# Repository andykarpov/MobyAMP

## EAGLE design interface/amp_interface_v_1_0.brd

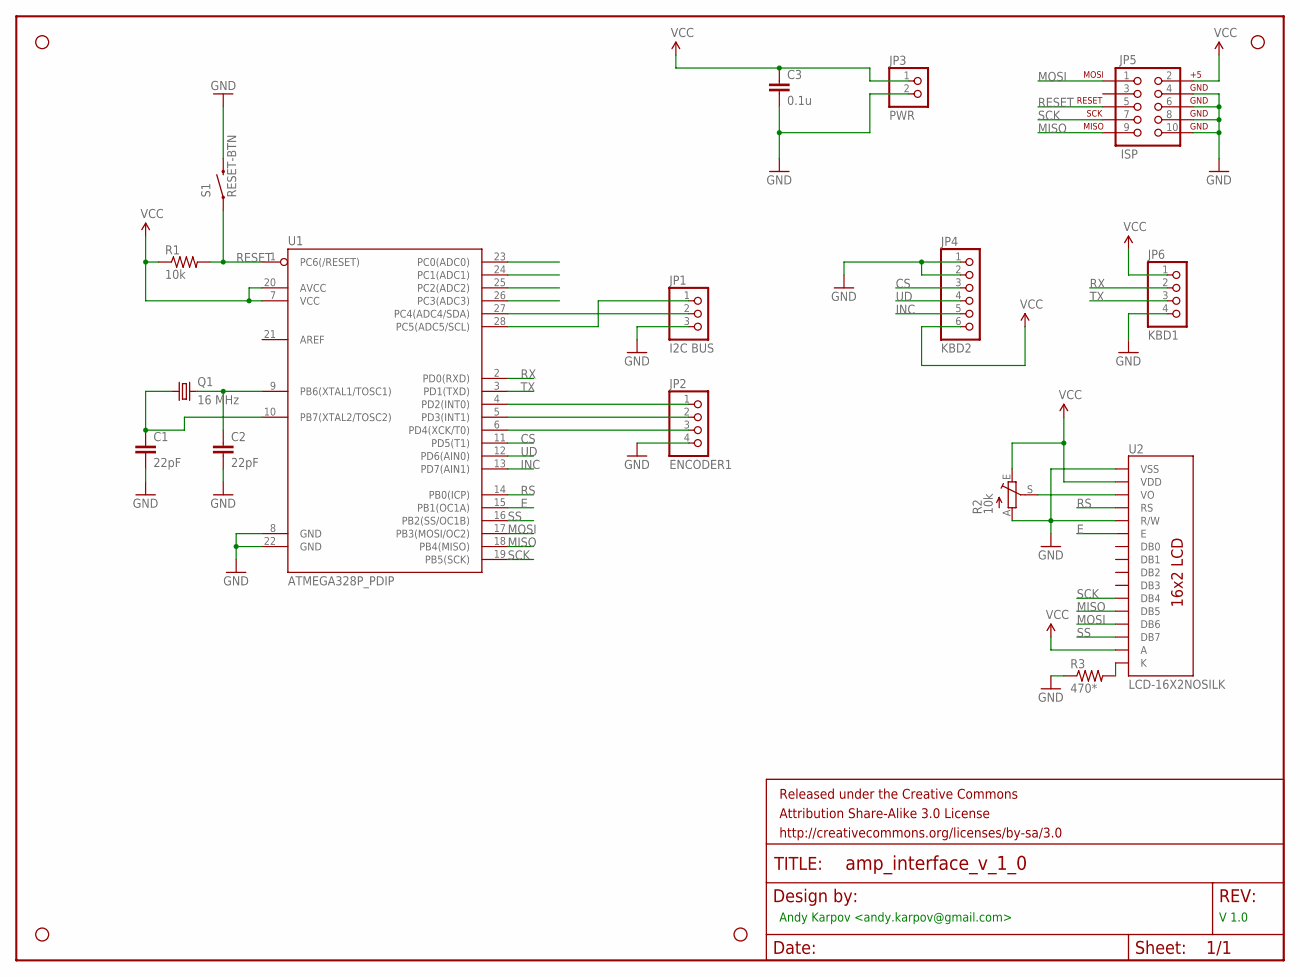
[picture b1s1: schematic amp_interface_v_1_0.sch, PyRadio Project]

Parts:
C1, C2: 22pF; CAP-PTH-SMALL2
C3: 0.1u; CAP-PTH-SMALL2
FRAME1: FRAME-LETTER; CREATIVE_COMMONS
JP1: I2C BUS; 1X03
JP2: ENCODER1; 1X04
JP3: PWR; 1X02
JP4: KBD2; 1X06
JP5: ISP; 2X5-SHROUDED
JP6: KBD1; 1X04
Q1: 16 MHz; HC49/S
R1: 10k; AXIAL-0.4
R2: 10k; B64Y
R3: 470*; AXIAL-0.4
S1: RESET-BTN; TACTILE-PTH
STANDOFF1, STANDOFF2, STANDOFF3, STANDOFF4: STAND-OFF
U1: ATMEGA328P_PDIP; DIL28-3
U2: LCD-16X2NOSILK; LCD-16X2_NOSILK

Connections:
CS: JP4.3, U1.11 (PD5(T1))
E: U1.15 (PB1(OC1A)), U2.6 (E)
GND: C1.2, C2.2, C3.2, JP1.3, JP2.4, JP3.2, JP4.1, JP4.2, JP5.4, JP5.6, JP5.8, JP5.10, JP6.4, R2.A, R3.P$1 (1), S1.3 (2), U1.8 (GND), U1.22 (GND), U2.1 (VSS), U2.5 (R/W)
INC: JP4.5, U1.13 (PD7(AIN1))
MISO: JP5.9, U1.18 (PB4(MISO)), U2.12 (DB5)
MOSI: JP5.1, U1.17 (PB3(MOSI/OC2)), U2.13 (DB6)
unnamed: C2.1, Q1.2, U1.9 (PB6(XTAL1/TOSC1))
unnamed: C1.1, Q1.1, U1.10 (PB7(XTAL2/TOSC2))
unnamed: R2.S, U2.3 (VO)
unnamed: R3.P$2 (2), U2.16 (K)
unnamed: JP1.2, U1.27 (PC4(ADC4/SDA))
unnamed: JP1.1, U1.28 (PC5(ADC5/SCL))
unnamed: JP2.3, U1.6 (PD4(XCK/T0))
unnamed: JP2.1, U1.4 (PD2(INT0))
unnamed: JP2.2, U1.5 (PD3(INT1))
PC0: U1.23 (PC0(ADC0))
PC1: U1.24 (PC1(ADC1))
PC2: U1.25 (PC2(ADC2))
PC3: U1.26 (PC3(ADC3))
RESET: JP5.5, R1.P$2 (2), S1.1, U1.1 (PC6(/RESET))
RS: U1.14 (PB0(ICP)), U2.4 (RS)
RX: JP6.2, U1.2 (PD0(RXD))
SCK: JP5.7, U1.19 (PB5(SCK)), U2.11 (DB4)
SS: U1.16 (PB2(SS/OC1B)), U2.14 (DB7)
TX: JP6.3, U1.3 (PD1(TXD))
UD: JP4.4, U1.12 (PD6(AIN0))
VCC: C3.1, JP3.1, JP4.6, JP5.2, JP6.1, R1.P$1 (1), R2.E, U1.7 (VCC), U1.20 (AVCC), U2.2 (VDD), U2.15 (A)

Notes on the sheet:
Andy Karpov <andy.karpov@gmail.com>
V 1.0

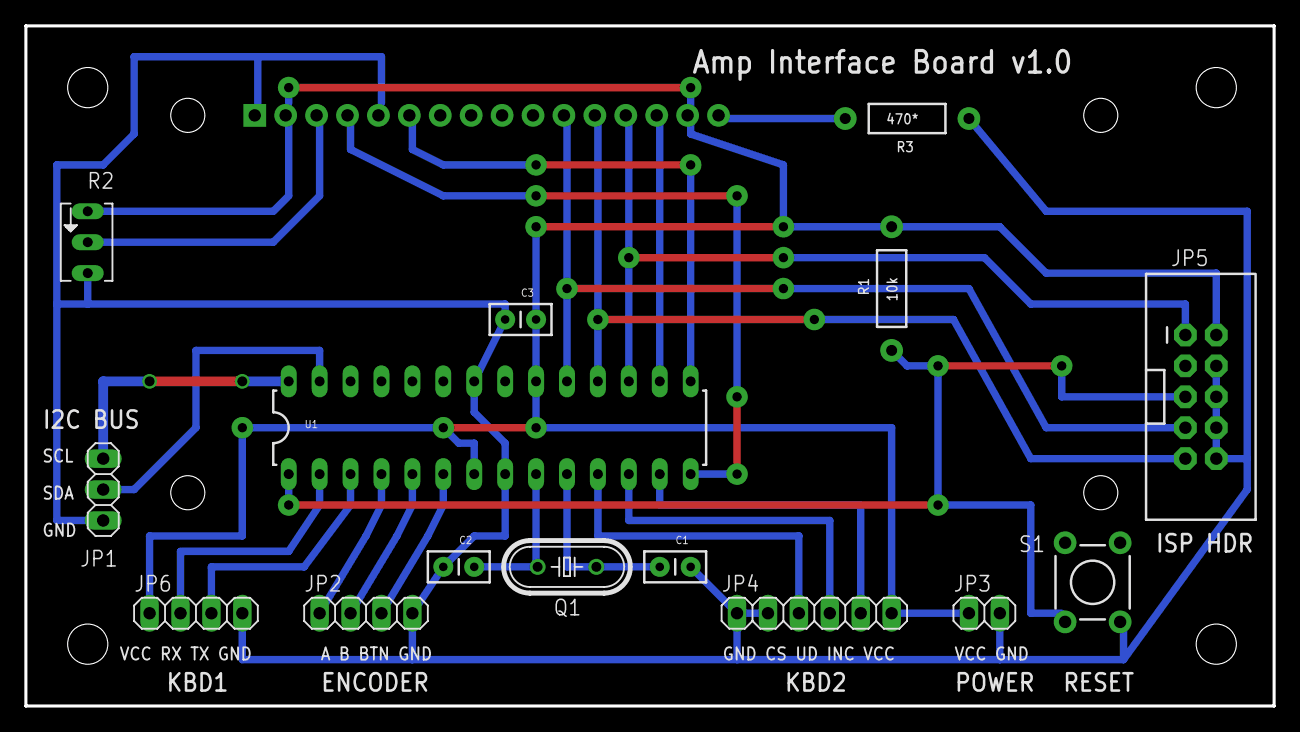
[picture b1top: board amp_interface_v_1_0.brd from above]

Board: 2 copper layers, 102.5 x 55.9 mm, 21 parts (0 on the bottom side), 23 nets.

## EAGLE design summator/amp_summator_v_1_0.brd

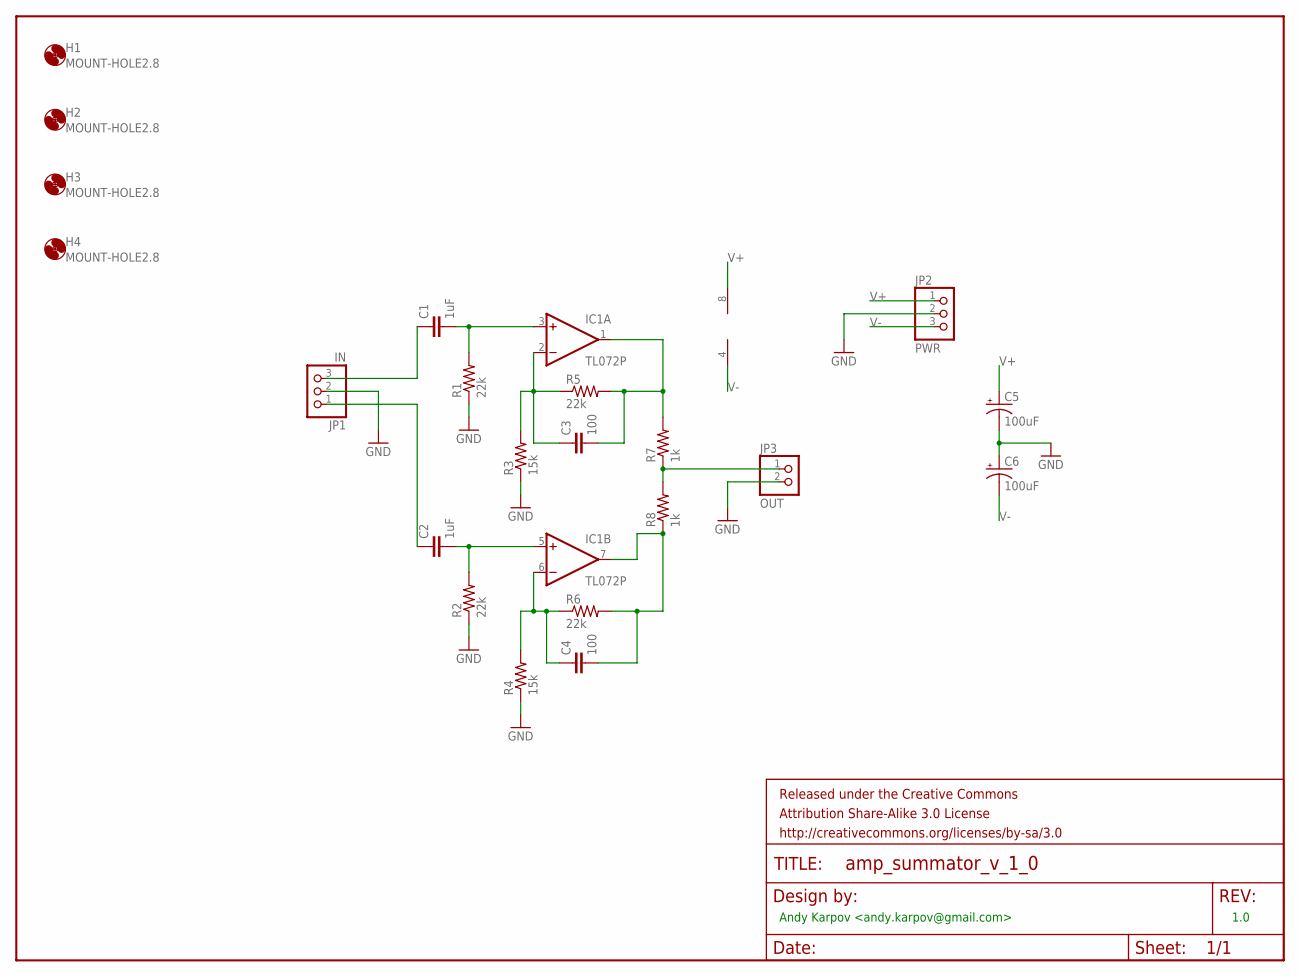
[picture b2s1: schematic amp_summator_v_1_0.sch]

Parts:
C1, C2: 1uF; CAP-PTH-5MM
C3, C4: 100; CAP-PTH-5MM
C5, C6: 100uF; CPOL-RADIAL-100UF-25V
FRAME1: FRAME-LETTER; CREATIVE_COMMONS
H1, H2, H3, H4: MOUNT-HOLE2.8; 2,8
IC1: TL072P; DIL08
JP1: IN; 1X03
JP2: PWR; 1X03
JP3: OUT; 1X02
R1, R2, R5, R6: 22k; AXIAL-0.4
R3, R4: 15k; AXIAL-0.4
R7, R8: 1k; AXIAL-0.4

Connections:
GND: C5.2 (-), C6.1 (+), JP1.2, JP2.2, JP3.2, R1.P$1 (1), R2.P$1 (1), R3.P$1 (1), R4.P$1 (1)
unnamed: C1.1, JP1.3
unnamed: JP3.1, R7.P$1 (1), R8.P$2 (2)
unnamed: C3.2, IC1.1 (OUT), R5.P$2 (2), R7.P$2 (2)
unnamed: C4.2, IC1.7 (OUT), R6.P$2 (2), R8.P$1 (1)
unnamed: C3.1, IC1.2 (-IN), R3.P$2 (2), R5.P$1 (1)
unnamed: C1.2, IC1.3 (+IN), R1.P$2 (2)
unnamed: C2.1, JP1.1
unnamed: C2.2, IC1.5 (+IN), R2.P$2 (2)
unnamed: C4.1, IC1.6 (-IN), R4.P$2 (2), R6.P$1 (1)
V+: C5.1 (+), IC1.8 (V+), JP2.1
V-: C6.2 (-), IC1.4 (V-), JP2.3

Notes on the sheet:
Andy Karpov <andy.karpov@gmail.com>
1.0

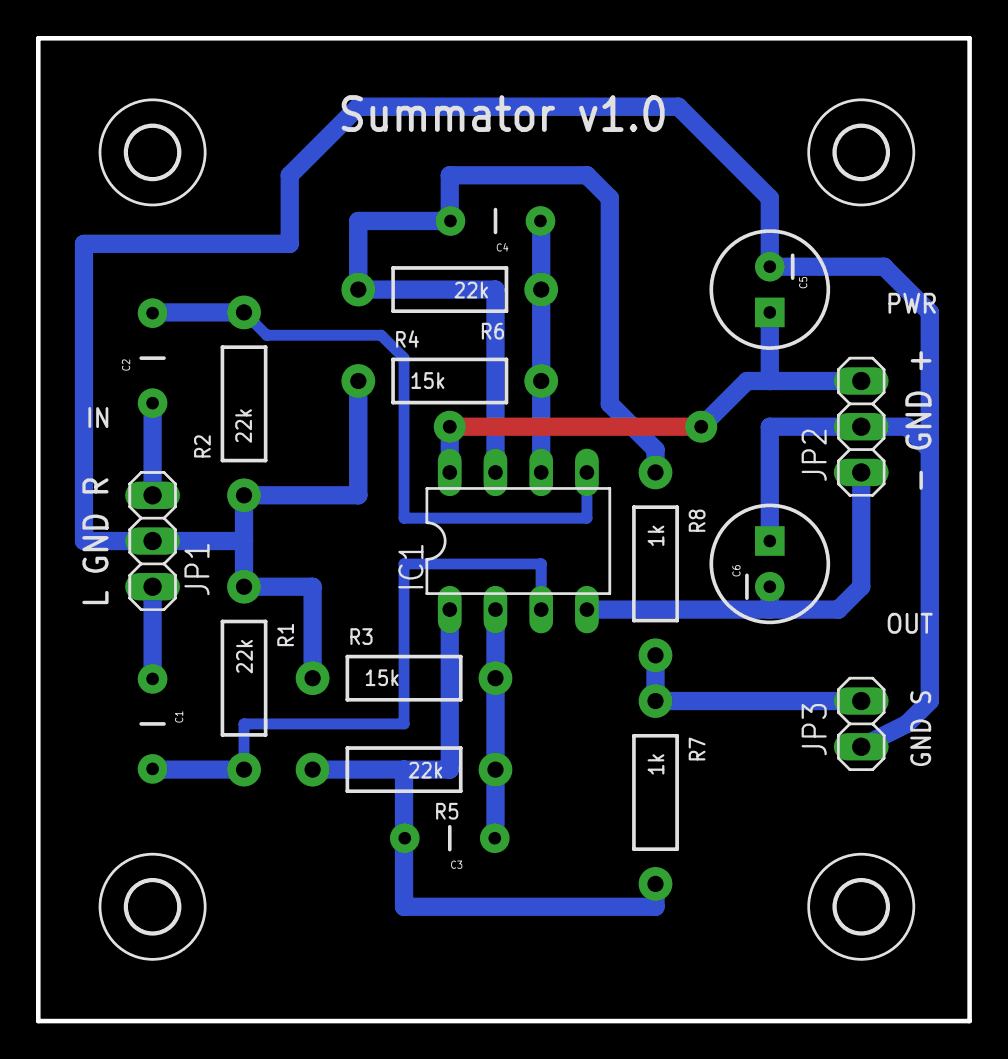
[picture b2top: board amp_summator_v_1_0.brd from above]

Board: 2 copper layers, 51.7 x 54.6 mm, 23 parts (0 on the bottom side), 12 nets.

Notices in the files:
parts and their libraries:
SparkFun-DigitalIC: Licensing: CC v3.0 Share-Alike You are welcome to use this library for commercial purposes.
SparkFun-Aesthetics: Released under the Creative Commons Attribution Share-Alike 3.0 License
SparkFun-Aesthetics: http://creativecommons.org/licenses/by-sa/3.0
